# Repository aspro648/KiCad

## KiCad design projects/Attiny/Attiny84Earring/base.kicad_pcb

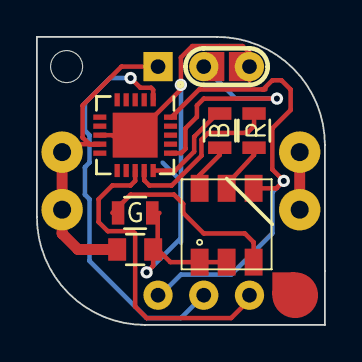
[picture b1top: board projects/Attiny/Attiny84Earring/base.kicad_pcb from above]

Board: 2 copper layers, 16.0 x 16.0 mm, 13 parts (1 on the bottom side), 11 nets.

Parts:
BT1: Battery; BATT_12mm_TH
C1: 0.1 uF; C_0805
D1: LED_RGB; LED_RGB_5050
IC1: ATTINY84A-M; QFN-20-1EP_4x4mm_Pitch0.5mm
P2: MISO; Pin_Header_Straight_1x01
P3: VCC; Pin_Header_Straight_1x01
P4: SCK; Pin_Header_Straight_1x01
P5: MOSI; Pin_Header_Straight_1x01
P6: RST; Pin_Header_Straight_1x01
P7: GND; Pin_Header_Straight_1x01
R1, R2, R3: R; R_0805

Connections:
+BATT: BT1.1, C1.1, IC1.9, P3.1
GND: BT1.2, C1.2, D1.1, D1.2, IC1.8, P7.1, R1.2
unnamed: D1.3, R1.1
unnamed: D1.4, IC1.20, P2.1
unnamed: D1.5, R2.2
unnamed: D1.6, R3.2
unnamed: IC1.1, P4.1
unnamed: IC1.13, P6.1
unnamed: IC1.14, R2.1
unnamed: IC1.15, R3.1
unnamed: IC1.16, P5.1

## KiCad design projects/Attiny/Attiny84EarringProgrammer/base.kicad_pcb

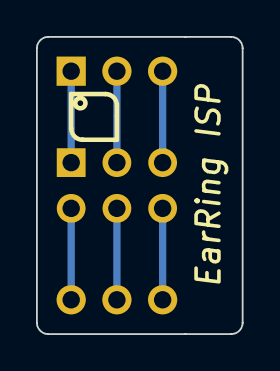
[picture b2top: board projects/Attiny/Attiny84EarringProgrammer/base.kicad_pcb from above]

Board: 2 copper layers, 11.4 x 16.5 mm, 7 parts (0 on the bottom side), 6 nets.

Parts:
CON1: AVR-ISP-6; DIP-6_W7.62mm
P2: MISO; Pin_Header_Straight_1x01
P3: VCC; Pin_Header_Straight_1x01
P4: SCK; Pin_Header_Straight_1x01
P5: MOSI; Pin_Header_Straight_1x01
P6: RST; Pin_Header_Straight_1x01
P7: GND; Pin_Header_Straight_1x01

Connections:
+BATT: CON1.2, P3.1
GND: CON1.6, P7.1
unnamed: CON1.1, P2.1
unnamed: CON1.3, P4.1
unnamed: CON1.4, P5.1
unnamed: CON1.5, P6.1

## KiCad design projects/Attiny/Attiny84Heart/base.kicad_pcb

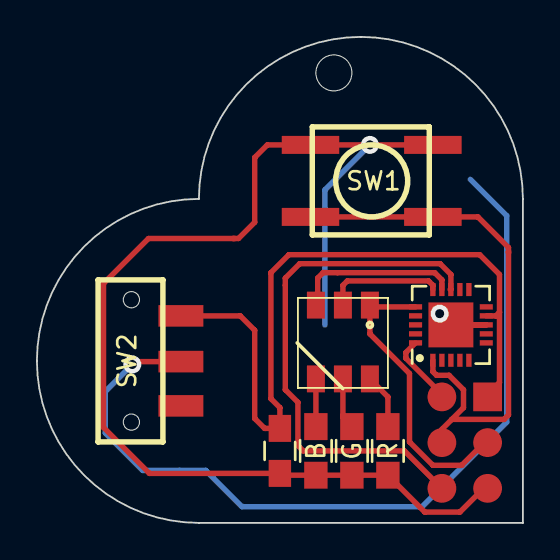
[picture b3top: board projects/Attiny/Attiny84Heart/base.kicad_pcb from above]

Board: 2 copper layers, 27.0 x 27.0 mm, 11 parts (1 on the bottom side), 12 nets.

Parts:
BT1: Battery; BATT_CR2032_SMD
C1: 0.1 uF; C_0805_HandSoldering
CON1: AVR-ISP-6
D1: LED_RGB; LED_RGB_QBLP679E
IC1: ATTINY84A-M; QFN-20-1EP_4x4mm_Pitch0.5mm
P1: CONN_01X01; Pin_Header_Straight_1x01
R1: R; R_0805_HandSoldering
R2: G; R_0805_HandSoldering
R3: B; R_0805_HandSoldering
SW1: SW_PUSH; SW_SMD_PUSH
SW2: SPST; SPST_SMD

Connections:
+BATT: C1.1, CON1.2, IC1.9, SW2.1
GND: BT1.2, C1.2, CON1.6, IC1.8, R1.2, R2.2, R3.2, SW1.2
unnamed: BT1.1, SW2.2
unnamed: CON1.1, IC1.20
unnamed: CON1.3, IC1.1, SW1.1
unnamed: CON1.4, D1.4, IC1.16
unnamed: CON1.5, IC1.13
unnamed: D1.1, R3.1
unnamed: D1.2, R2.1
unnamed: D1.3, R1.1
unnamed: D1.5, IC1.15
unnamed: D1.6, IC1.14

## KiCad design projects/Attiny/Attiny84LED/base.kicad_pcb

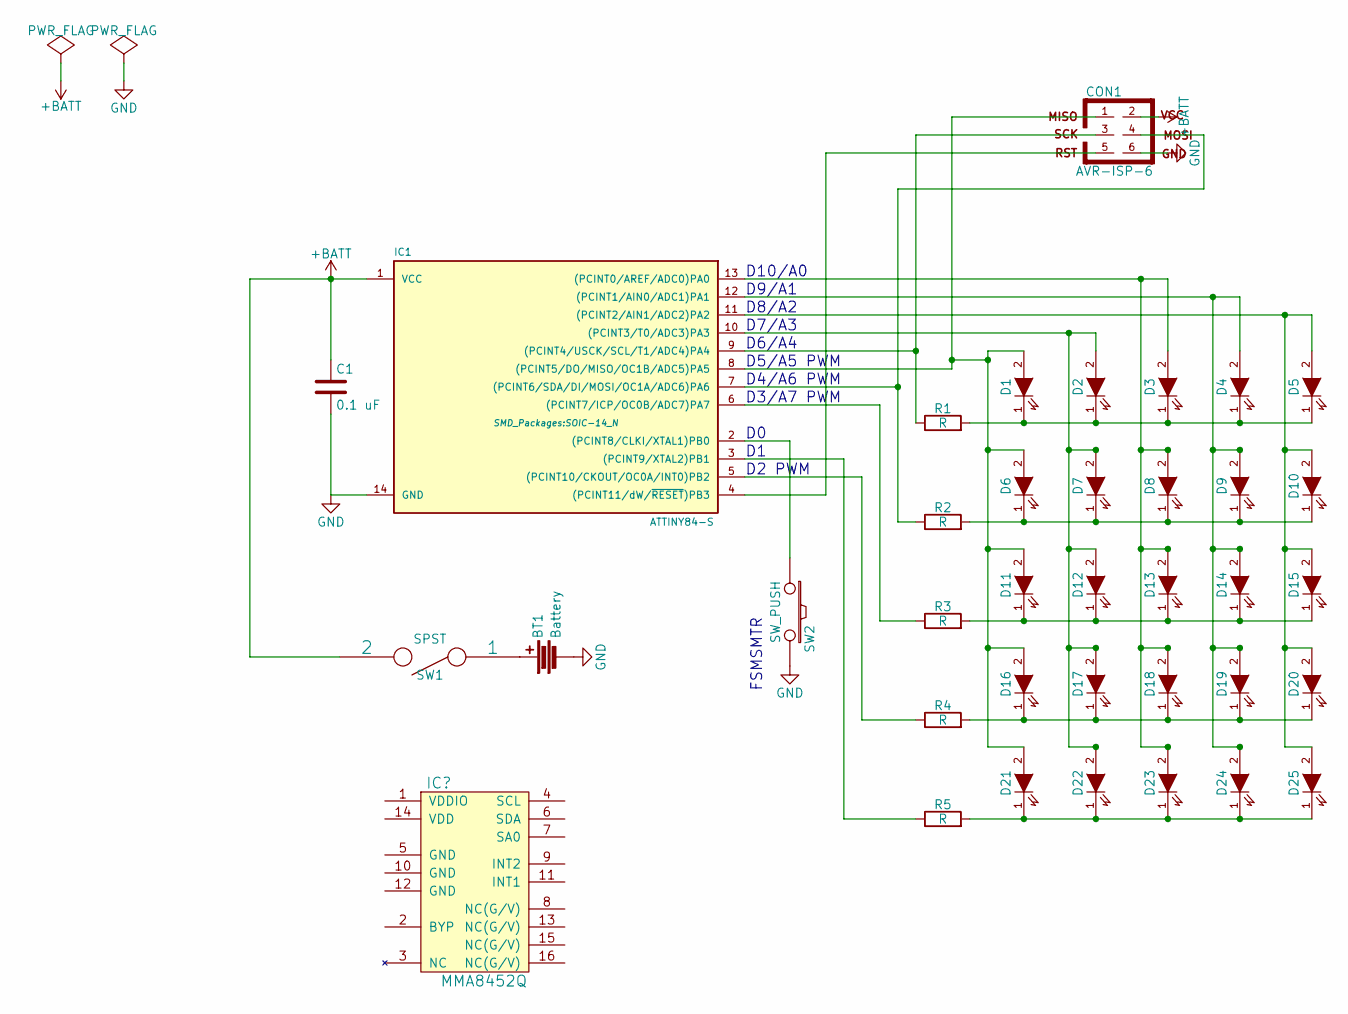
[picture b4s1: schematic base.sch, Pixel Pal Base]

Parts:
BT1: Battery; BATT_CR2032_SMD
C1: 0.1 uF; C_1206
CON1: AVR-ISP-6; Pin_Header_Straight_2x03
D1, D2, D3, D4, D5, D6, D7, D8, D9, D10, D11, D12, D13, D14, D15, D16, D17, D18, D19, D20, D21, D22, D23, D24, D25: LED; LED-1206
IC1: ATTINY84-S; SOIC-14_N
R1, R2, R3, R4, R5: R; R_1206
SW1: SPST; mySwitchDPDT
SW2: SW_PUSH; SW_SPST_EVQPE1

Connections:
+BATT: C1.1, CON1.2, IC1.1 (VCC), SW1.2
GND: BT1.2, C1.2, CON1.6, IC1.14 (GND), SW2.2
unnamed: BT1.1, SW1.1
unnamed: CON1.1, D1.2 (A), D6.2 (A), D11.2 (A), D16.2 (A), D21.2 (A), IC1.8 ((PCINT5/DO/MISO/OC1B/ADC5)PA5)
unnamed: CON1.3, IC1.9 ((PCINT4/USCK/SCL/T1/ADC4)PA4), R1.1
unnamed: CON1.4, IC1.7 ((PCINT6/SDA/DI/MOSI/OC1A/ADC6)PA6), R2.1
unnamed: CON1.5, IC1.4 ((PCINT11/dW/~RESET~)PB3)
unnamed: D1.1 (K), D2.1 (K), D3.1 (K), D4.1 (K), D5.1 (K), R1.2
unnamed: D6.1 (K), D7.1 (K), D8.1 (K), D9.1 (K), D10.1 (K), R2.2
unnamed: D5.2 (A), D10.2 (A), D15.2 (A), D20.2 (A), D25.2 (A), IC1.11 ((PCINT2/AIN1/ADC2)PA2)
unnamed: D11.1 (K), D12.1 (K), D13.1 (K), D14.1 (K), D15.1 (K), R3.2
unnamed: D2.2 (A), D7.2 (A), D12.2 (A), D17.2 (A), D22.2 (A), IC1.10 ((PCINT3/T0/ADC3)PA3)
unnamed: D3.2 (A), D8.2 (A), D13.2 (A), D18.2 (A), D23.2 (A), IC1.13 ((PCINT0/AREF/ADC0)PA0)
unnamed: D4.2 (A), D9.2 (A), D14.2 (A), D19.2 (A), D24.2 (A), IC1.12 ((PCINT1/AIN0/ADC1)PA1)
unnamed: D16.1 (K), D17.1 (K), D18.1 (K), D19.1 (K), D20.1 (K), R4.2
unnamed: D21.1 (K), D22.1 (K), D23.1 (K), D24.1 (K), D25.1 (K), R5.2
unnamed: IC1.2 ((PCINT8/CLKI/XTAL1)PB0), SW2.1
unnamed: IC1.3 ((PCINT9/XTAL2)PB1), R5.1
unnamed: IC1.5 ((PCINT10/CKOUT/OC0A/INT0)PB2), R4.1
unnamed: IC1.6 ((PCINT7/ICP/OC0B/ADC7)PA7), R3.1

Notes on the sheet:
D2 PWM
D4/A6 PWM
D3/A7 PWM
D5/A5 PWM
D6/A4
D7/A3
D8/A2
D9/A1
D10/A0
FSMSMTR

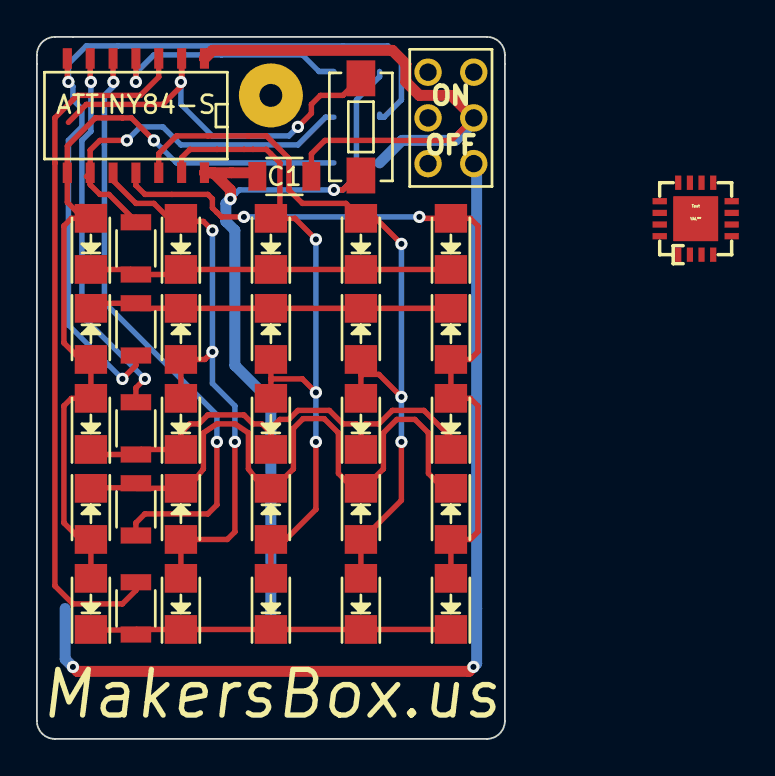
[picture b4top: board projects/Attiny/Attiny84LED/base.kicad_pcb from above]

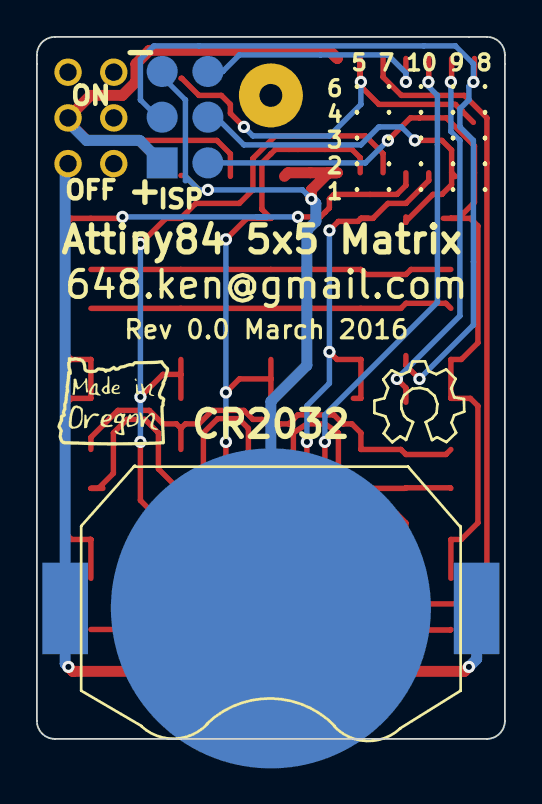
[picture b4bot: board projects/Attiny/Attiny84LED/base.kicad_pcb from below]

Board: 2 copper layers, 26.0 x 39.0 mm, 38 parts (2 on the bottom side), 20 nets.

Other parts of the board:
Test: VAL**; QFN-16
VAL: MadeInOregonRev25

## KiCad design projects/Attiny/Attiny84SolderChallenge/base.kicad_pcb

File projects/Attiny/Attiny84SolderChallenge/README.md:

Introduction
============

Test your soldering skills, starting with standard through-hole components and work your way down into smaller and smaller surface mount components.  If you only get the through-hole components to light, you will still be greeted with a surprise if you spin the board on a pencil! 

Bill Of Materials
=================
  
- 1 ea., Perfect Purple PCB from OSH Park
- 1 ea., ATTINY24/44/84 14-PDIP (1.8V ~ 5.5V) https://www.digikey.com/short/zqwhcw
- 1 ea., CAP CER 0.1UF 
- 1 ea., SWITCH TACTILE SPST-NO 0.05A 24V, https://www.digikey.com/short/zqwh7q
- 1 ea., SPST Slide switch, EG1270, https://www.digikey.com/short/zqwh83
- 1 ea., 5mm LED Green diffuse, https://www.digikey.com/short/zqwh4h
- 1 ea., 100 OHM 1/4W resistor, https://www.digikey.com/short/zqwhp4
- 1 ea., 3mm LED Yellow diffuse, https://www.digikey.com/short/zqwhmf
- 1 ea., 100 OHM 1/6W resistor, https://www.digikey.com/short/zqwhpr
- 1 ea., LED RED CLEAR 1206 SMD, Lite-On LTST-C150KRKT, https://www.digikey.com/short/3253m7
- 1 ea., RES SMD 100 OHM 5% 1/4W 1206, Digiket P100ECT-ND
- 1 ea., LED ORANGE CLEAR 0805 SMD, https://www.digikey.com/short/qjwthb
- 1 ea., RES SMD 100 OHM 5% 1/8W 0805, https://www.digikey.com/short/z7nv19
- 1 ea., LED YELLOW CLEAR 0603 SMD, Lite-On LTST-C191KSKT, https://www.digikey.com/short/3wzzr2
- 1 ea., RES SMD 100 OHM 5% 1/10W 0603, https://www.digikey.com/short/z7n1cv
- 1 ea., LED GREEN CLEAR 0402 SMD, SunLED XZVG68W-2, https://www.digikey.com/short/3wzzfm
- 1 ea., RES 100 OHM 5% 1/16W 0402, https://www.digikey.com/short/z7n132
- 1 ea., LED BLUE CLEAR 0201 SMD, Kingbright APG0603PBC-TT-5MAV, https://www.digikey.com/short/3wzzfr
- 1 ea., RES SMD 100 OHM 5% 1/20W 0201, https://www.digikey.com/short/z7n18r

- 1 ea., BATTERY RETAINER COIN PC PIN, https://www.digikey.com/short/zqwh7h
- 1 ea. CR2032 Battery, Panasonic CR2032, Digikey P189-ND (requires ground shipping, or buy locally).

Design Files
============
This project is designed using Open Source [KiCad](http://kicad-pcb.org/). Design files are located in the [design_files](design_files/) folder.  You can oogle the [schematic](images/project.sch.png).

Firmware
========
This project is programed using the Open Source [Arduino](https://www.arduino.cc/). I use my Open Source [AVR Programming Shield](https://www.tindie.com/products/MakersBox/yet-another-programming-shield/) to program the Attiny. The firmware is located in the [firmware](firmware/) folder.

Assembly Instructions
=====================
TBD

License
=======
[Attribution-ShareAlike 3.0 United States (CC BY-SA 3.0 US)](https://creativecommons.org/licenses/by-sa/3.0/us/)

You are free to:

- Share — copy and redistribute the material in any medium or format
- Adapt — remix, transform, and build upon the material

Under the following terms:

- Attribution — You must give appropriate credit, provide a link to the license, and indicate if changes were made. You may do so in any reasonable manner, but not in any way that suggests the licensor endorses you or your use.
- ShareAlike — If you remix, transform, or build upon the material, you must distribute your contributions under the same license as the original.

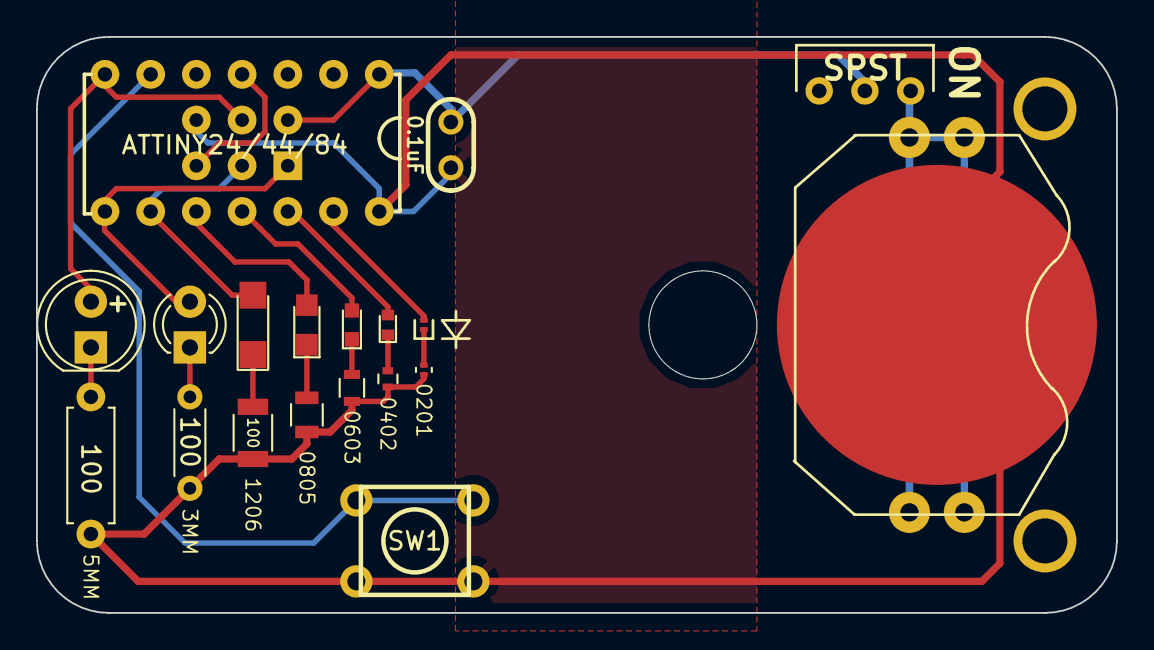
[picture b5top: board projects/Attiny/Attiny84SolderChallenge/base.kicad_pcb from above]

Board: 2 copper layers, 60.0 x 32.0 mm, 20 parts (1 on the bottom side), 19 nets.

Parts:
BT1: Battery; BATT_CR2032
C1: 0.1 uF; C1
CON1: AVR-ISP-6
D0: LED; LED_0201
D1: LED; LED_0402
D2: LED; LED_0603
D3: LED; LED_0805
D4: LED; LED_1206
D5: LED; LED_D3.0mm
D6: LED; LED_D5.0mm
IC1: ATTINY84-S; DIP-14_W7.62mm
R0: 100; R_0201
R1: 100; R_0402
R2: 100; R_0603
R3: 100; R_0805
R4: 100; R_1206
R5: 100; R_Axial_DIN0204_L3.6mm_D1.6mm_P5.08mm_Horizontal
R6: 100; R_Axial_DIN0207_L6.3mm_D2.5mm_P7.62mm_Horizontal
SW1: SW_PUSH; SW_PUSH_SMALL
SW2: SPST; SW_SPST

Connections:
+BATT: C1.1, CON1.2, IC1.1, SW2.2
GND: BT1.2, C1.2, CON1.6, IC1.14, R0.2, R1.2, R2.2, R3.2, R4.2, R5.2, R6.2, SW1.2
unnamed: BT1.1, SW2.1
unnamed: CON1.1, D5.2, IC1.8
unnamed: CON1.3, D4.2, IC1.9
unnamed: CON1.4, D6.2, IC1.7
unnamed: CON1.5, IC1.4
unnamed: D0.1, R0.1
unnamed: D0.2, IC1.13
unnamed: D1.1, R1.1
unnamed: D1.2, IC1.12
unnamed: D2.1, R2.1
unnamed: D2.2, IC1.11
unnamed: D3.1, R3.1
unnamed: D3.2, IC1.10
unnamed: D4.1, R4.1
unnamed: D5.1, R5.1
unnamed: D6.1, R6.1
unnamed: IC1.6, SW1.1
